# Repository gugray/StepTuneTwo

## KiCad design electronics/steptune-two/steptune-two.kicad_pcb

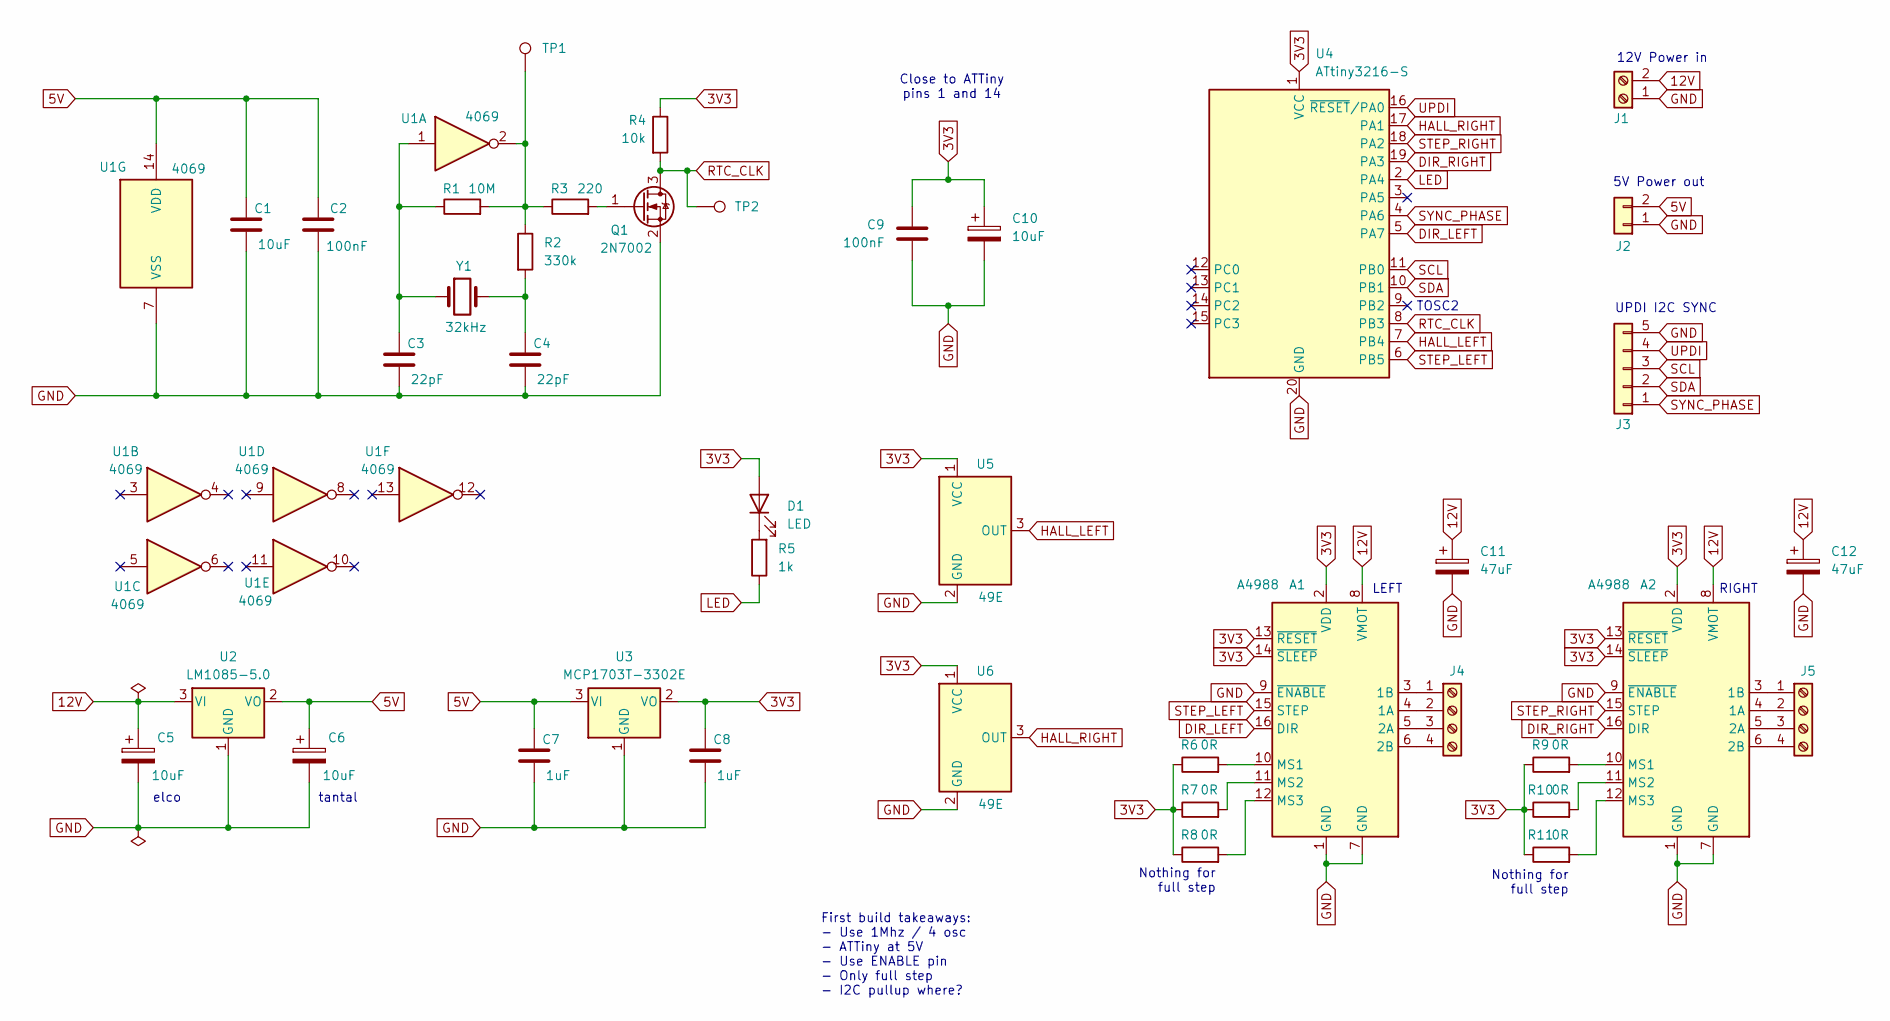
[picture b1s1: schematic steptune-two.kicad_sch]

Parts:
A1, A2: A4988; Pololu_Breakout-16_15.2x20.3mm
C1, C10: 10uF; C_0805_2012Metric
C2, C9: 100nF; C_0805_2012Metric
C3, C4: 22pF; C_1206_3216Metric
C5, C6: 10uF; CP_Radial_D5.0mm_P2.50mm
C7, C8: 1uF; C_0805_2012Metric
C11, C12: 47uF; CP_Radial_D6.3mm_P2.50mm
D1: LED; LED_0805_2012Metric
J1: Screw_Terminal_01x02; TerminalBlock_4Ucon_1x02_P3.50mm_Horizontal
J2: Conn_01x02; PinHeader_1x02_P2.54mm_Vertical
J3: Conn_01x05; PinHeader_1x05_P2.54mm_Vertical
J4, J5: Screw_Terminal_01x04; TerminalBlock_4Ucon_1x04_P3.50mm_Horizontal
Q1: 2N7002; SOT-23
R1: 10M; R_0805_2012Metric
R2: 330k; R_0805_2012Metric
R3: 220; R_0805_2012Metric
R4: 10k; R_0805_2012Metric
R5: 1k; R_0805_2012Metric
R6, R7, R8, R9, R10, R11: 0R; R_0805_2012Metric
TP1, TP2: TestPoint; TestPoint_Pad_D1.5mm
U1: 4069; SO-14_3.9x8.65mm_P1.27mm
U2: LM1085-5.0; TO-220-3_Vertical
U3: MCP1703T-3302E; SOT-23
U4: ATtiny3216-S; SOIC-20W_7.5x12.8mm_P1.27mm
U5, U6: 49E; TO-92_Inline
Y1: 32kHz; Crystal_Round_D1.5mm_Vertical

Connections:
3V3: A1.2 (VDD), A1.13 (~RESET), A1.14 (~SLEEP), A2.2 (VDD), A2.13 (~RESET), A2.14 (~SLEEP), C8.1, C9.1, C10.1, D1.2 (A), R4.1, R6.1, R7.1, R8.1, R9.1, R10.1, R11.1, U3.2 (VO), U4.1 (VCC), U5.1 (VCC), U6.1 (VCC)
5V: C1.1, C2.1, C6.1, C7.1, J2.2, U1.14 (VDD), U2.2 (VO), U3.3 (VI)
12V: A1.8 (VMOT), A2.8 (VMOT), C5.1, C11.1, C12.1, J1.2, U2.3 (VI)
DIR_LEFT: A1.16 (DIR), U4.5 (PA7)
DIR_RIGHT: A2.16 (DIR), U4.19 (PA3)
GND: A1.1 (GND), A1.7 (GND), A1.9 (~ENABLE), A2.1 (GND), A2.7 (GND), A2.9 (~ENABLE), C1.2, C2.2, C3.2, C4.2, C5.2, C6.2, C7.2, C8.2, C9.2, C10.2, C11.2, C12.2, J1.1, J2.1, J3.5, Q1.2 (S), U1.7 (VSS), U2.1 (GND), U3.1 (GND), U4.20 (GND), U5.2 (GND), U6.2 (GND)
HALL_LEFT: U4.7 (PB4), U5.3 (OUT)
HALL_RIGHT: U4.17 (PA1), U6.3 (OUT)
LED: R5.1, U4.2 (PA4)
unnamed: A1.4 (1A), J4.2
unnamed: A1.3 (1B), J4.1
unnamed: A1.5 (2A), J4.3
unnamed: A1.6 (2B), J4.4
unnamed: A1.10 (MS1), R6.2
unnamed: A1.11 (MS2), R7.2
unnamed: A1.12 (MS3), R8.2
unnamed: A2.4 (1A), J5.2
unnamed: A2.3 (1B), J5.1
unnamed: A2.5 (2A), J5.3
unnamed: A2.6 (2B), J5.4
unnamed: A2.10 (MS1), R9.2
unnamed: A2.11 (MS2), R10.2
unnamed: A2.12 (MS3), R11.2
unnamed: C3.1, R1.1, U1.1, Y1.1
unnamed: C4.1, R2.2, Y1.2
unnamed: D1.1 (K), R5.2
unnamed: Q1.1 (G), R3.2
unnamed: R1.2, R2.1, R3.1, TP1.1, U1.2
RTC_CLK: Q1.3 (D), R4.2, TP2.1, U4.8 (PB3)
SCL: J3.3, U4.11 (PB0)
SDA: J3.2, U4.10 (PB1)
STEP_LEFT: A1.15 (STEP), U4.6 (PB5)
STEP_RIGHT: A2.15 (STEP), U4.18 (PA2)
SYNC_PHASE: J3.1, U4.4 (PA6)
UPDI: J3.4, U4.16 (~RESET/PA0)

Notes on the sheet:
TOSC2
12V Power in
UPDI I2C SYNC
LEFT
tantal
Nothing for full step
RIGHT
First build takeaways: - Use 1Mhz / 4 osc - ATTiny at 5V - Use ENABLE pin - Only full step - I2C pullup where?
elco
5V Power out
Close to ATTiny pins 1 and 14

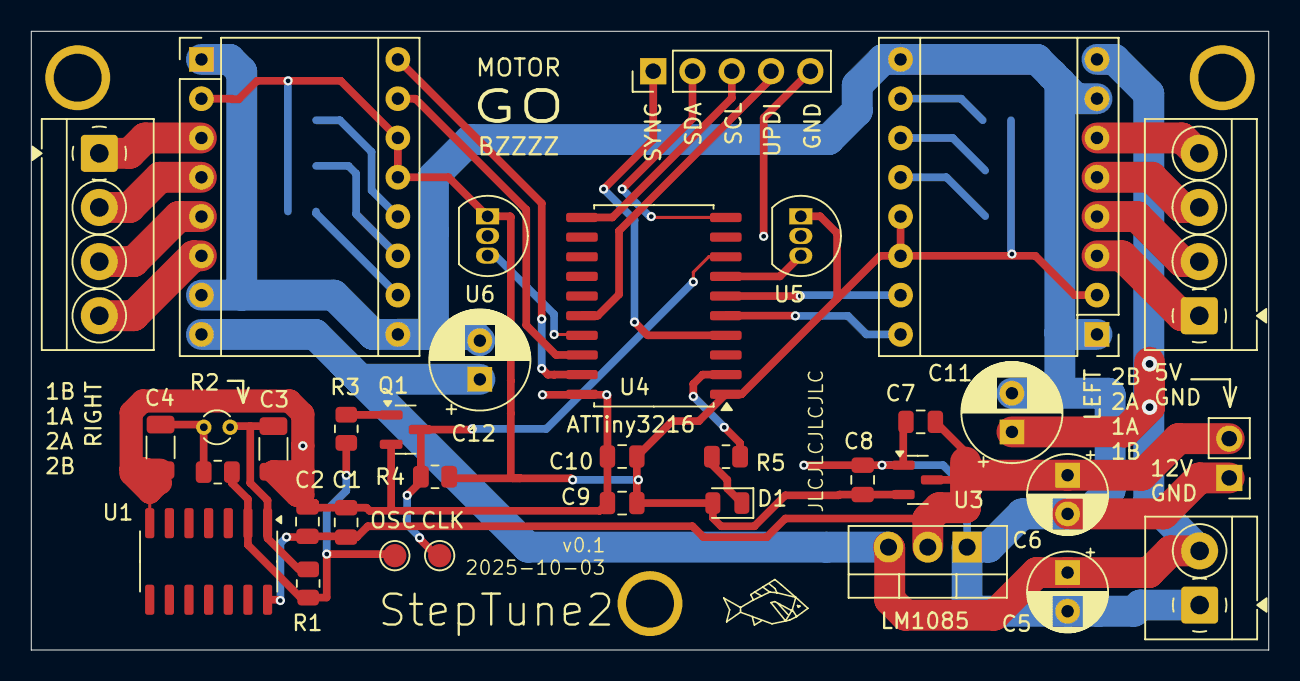
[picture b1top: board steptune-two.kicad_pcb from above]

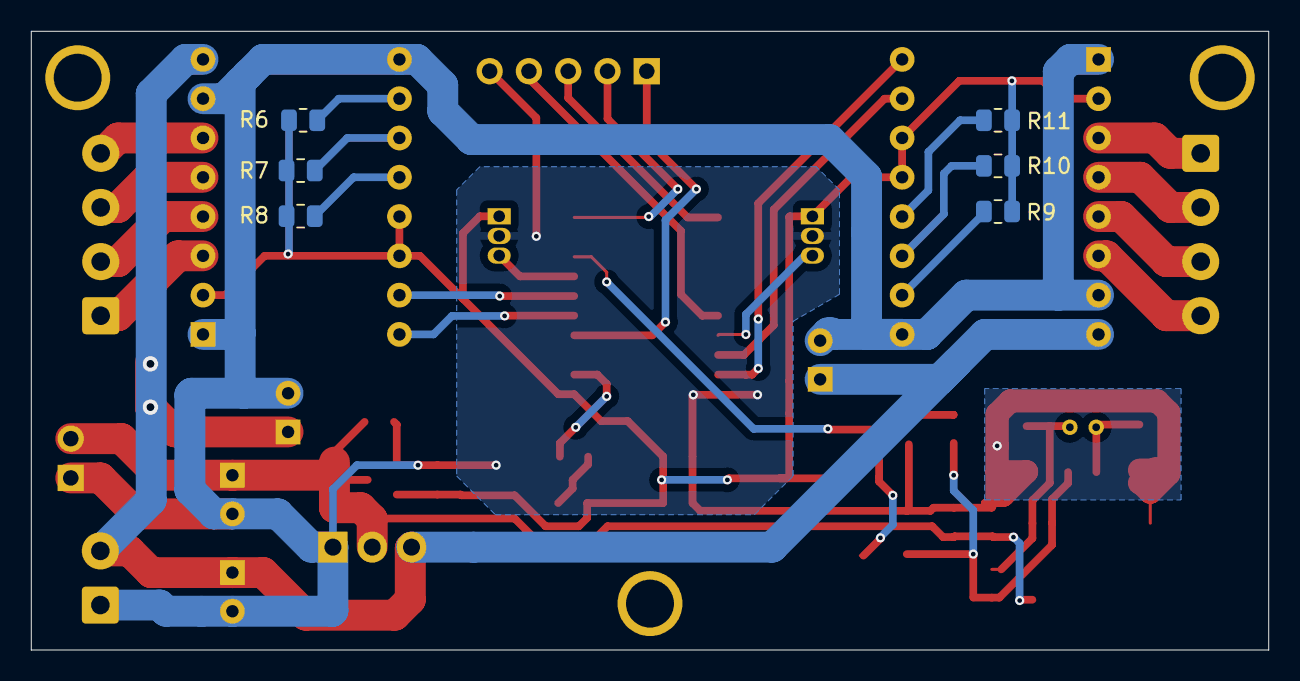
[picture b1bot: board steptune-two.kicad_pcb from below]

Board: 2 copper layers, 80.0 x 40.0 mm, 41 parts (6 on the bottom side), 35 nets.

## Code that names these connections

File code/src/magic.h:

#ifndef MAGIC_H
#define MAGIC_H

// clang-format off

#define ONBOARD_LED_PIN     PIN_PA4
#define RMOT_DIR_PIN        PIN_PA3
#define RMOT_STEP_PIN       PIN_PA2
#define LMOT_DIR_PIN        PIN_PA7
#define LMOT_STEP_PIN       PIN_PB5

#endif

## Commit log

2025-10-29 initial commit / working prototype
2025-12-16 physical design
2025-12-27 additional references
2025-12-27 notes; experiment with larger motor
2025-12-27 updated wings for larger motor
2026-01-09 more wings updates
2026-01-13 embedded sketches for play
2026-01-13 code -> code-mcu
2026-01-13 added skeleton raspi code
2026-01-13 control LED GPIO
2026-01-15 send i2c commands
2026-01-15 timer counter, no interrupt; listen for i2c
2026-01-16 rought send period on i2c
2026-01-16 period over i2c; no arduino fx
